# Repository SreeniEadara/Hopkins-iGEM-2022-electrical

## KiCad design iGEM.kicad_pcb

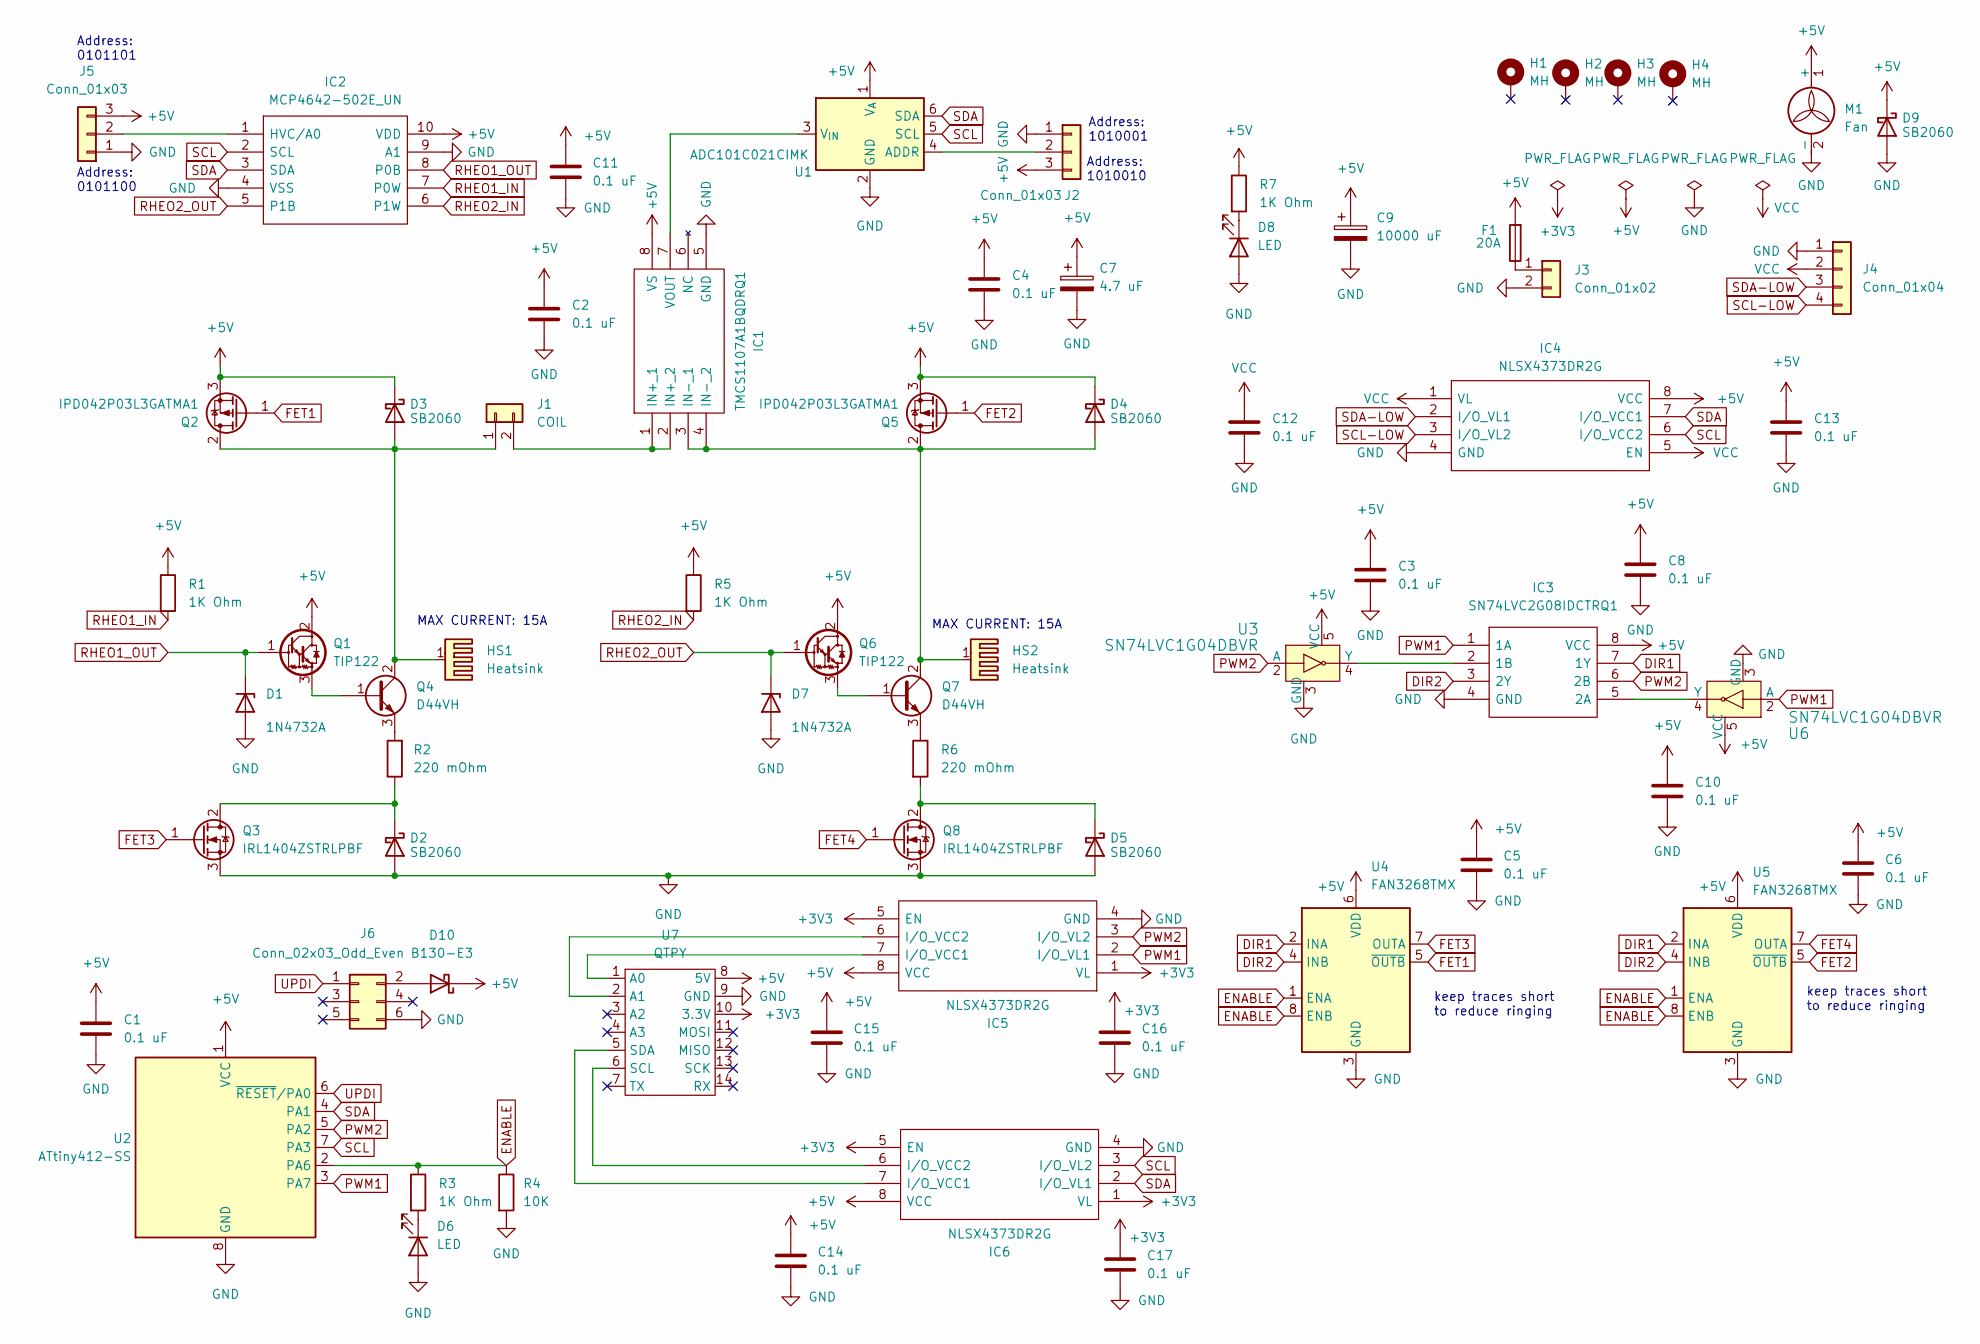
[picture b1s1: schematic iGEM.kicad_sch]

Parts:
C1, C2, C3, C4, C5, C6, C8, C10, C11, C12, C13, C14, C15, C16, C17: 0.1 uF; C_0805_2012Metric_Pad1.18x1.45mm_HandSolder; DigiKey 399-C0805C104K8RAC7800CT-ND
C7: 4.7 uF; CP_EIA-3528-21_Kemet-B_Pad1.50x2.35mm_HandSolder; DigiKey 399-3723-1-ND
C9: 10000 uF; CP_Radial_D22.0mm_P10.00mm_SnapIn; DigiKey 399-ELG109M025AQ4AA-ND
D1, D7: 1N4732A; D_DO-41_SOD81_P10.16mm_Horizontal; DigiKey 1N4732AFSCT-ND
D2, D3, D4, D5, D9: SB2060; D_DO-201AD_P12.70mm_Horizontal; DigiKey 1655-SB2060CT-ND
D6, D8: LED; LED_0805_2012Metric_Pad1.15x1.40mm_HandSolder; DigiKey 475-1410-1-ND
D10: B130-E3; D_SMA; DigiKey B130-E3/5ATGICT-ND
F1: 20A; Fuseholder_Blade_Mini_Keystone_3568; DigiKey 36-3568-15-ND
H1, H2, H3, H4: MH; MountingHole_3.2mm_M3_DIN965_Pad
HS1, HS2: Heatsink; Heatsink_Fischer_SK104-STC-STIC_35x13mm_2xDrill2.5mm; DigiKey HS403-ND
IC1: TMCS1107A1BQDRQ1; SOIC-8_3.9x4.9mm_P1.27mm; Manufacturer_Part_Number TMCS1107A1BQDRQ1; DigiKey 296-TMCS1107A1BQDRQ1CT-ND
IC2: MCP4642-502E_UN; SOP50P490X110-10N; Manufacturer_Part_Number MCP4642-502E/UN; Mouser Part Number 579-MCP4642-502E/UN
IC3: SN74LVC2G08IDCTRQ1; MSOP-8_3x3mm_P0.65mm; Manufacturer_Part_Number SN74LVC2G08IDCTRQ1; Mouser Part Number 595-SN74LVC2G08IDCQ1
IC4, IC5, IC6: NLSX4373DR2G; SOIC-8_3.9x4.9mm_P1.27mm; Manufacturer_Part_Number NLSX4373DR2G; Mouser Part Number 863-NLSX4373DR2G
J1: COIL; TerminalBlock_bornier-2_P5.08mm; DigiKey 102-6218-ND
J2, J5: Conn_01x03; PinHeader_1x03_P2.54mm_Vertical
J3: Conn_01x02; 8PCV02006; DigiKey A98460-ND
J4: Conn_01x04; JST_XH_B4B-XH-A_1x04_P2.50mm_Vertical; DigiKey 455-2249-ND
J6: Conn_02x03_Odd_Even; PinHeader_2x03_P2.54mm_Vertical
M1: Fan; JST_XH_B2B-XH-A_1x02_P2.50mm_Vertical; DigiKey 455-2879-ND
Q1, Q6: TIP122; TO-220-3_Horizontal_TabDown; DigiKey TIP122GOS-ND
Q2, Q5: IPD042P03L3GATMA1; TO-252-2; DigiKey IPD042P03L3GATMA1CT-ND
Q3, Q8: IRL1404ZSTRLPBF; TO-263-2; DigiKey IRL1404ZSTRLPBFCT-ND
Q4, Q7: D44VH; TO-220-3_Vertical; DigiKey D44VH10GOS-ND
R1, R3, R5, R7: 1K Ohm; R_0805_2012Metric_Pad1.20x1.40mm_HandSolder; DigiKey CHP0805-FX-1001ELFCT-ND
R2, R6: 220 mOhm; TerminalBlock_bornier-2_P5.08mm; DigiKey A102180-ND
R4: 10K; R_0805_2012Metric_Pad1.20x1.40mm_HandSolder; DigiKey RMCF0805FT10K0CT-ND
U1: ADC101C021CIMK; SOT-23-6; DigiKey ADC101C021CIMK/NOPBCT-ND
U2: ATtiny412-SS; SOIC-8_3.9x4.9mm_P1.27mm; DigiKey ATTINY412-SSN-ND
U3, U6: SN74LVC1G04DBVR; SOT-753; MPN SN74LVC1G04DBVR; Digi-Key_PN 296-11599-1-ND
U4, U5: FAN3268TMX; SOIC-8_3.9x4.9mm_P1.27mm; DigiKey FAN3268TMXCT-ND
U7: QTPY; QTPY-RP2040

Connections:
+3V3: C16.1, C17.1, IC5.1 (VL), IC5.5 (EN), IC6.1 (VL), IC6.5 (EN), U7.10 (3.3V)
+5V: C1.1, C2.1, C3.1, C4.1, C5.1, C6.1, C7.1, C8.1, C9.1, C10.1, C11.1, C13.1, C14.1, C15.1, D3.1 (K), D4.1 (K), D9.1 (K), D10.1 (K), F1.2, IC1.8 (VS), IC2.10 (VDD), IC3.8 (VCC), IC4.8 (VCC), IC5.8 (VCC), IC6.8 (VCC), J2.3, J5.3, M1.1 (+), Q1.2 (C), Q2.3 (S), Q5.3 (S), Q6.2 (C), R1.1, R5.1, R7.1, U1.1 (V_{A}), U2.1 (VCC), U3.5 (VCC), U4.6 (VDD), U5.6 (VDD), U6.5 (VCC), U7.8 (5V)
DIR1: IC3.7 (1Y), U4.2 (INA), U5.2 (INA)
DIR2: IC3.3 (2Y), U4.4 (INB), U5.4 (INB)
ENABLE: R3.1, R4.1, U2.2 (PA6), U4.1 (ENA), U4.8 (ENB), U5.1 (ENA), U5.8 (ENB)
FET1: Q2.1 (G), U4.5 (~OUTB)
FET2: Q5.1 (G), U5.5 (~OUTB)
FET3: Q3.1 (G), U4.7 (OUTA)
FET4: Q8.1 (G), U5.7 (OUTA)
GND: C1.2, C2.2, C3.2, C4.2, C5.2, C6.2, C7.2, C8.2, C9.2, C10.2, C11.2, C12.2, C13.2, C14.2, C15.2, C16.2, C17.2, D1.2 (A), D2.2 (A), D5.2 (A), D6.2 (A), D7.2 (A), D8.2 (A), D9.2 (A), IC1.5 (GND), IC2.4 (VSS), IC2.9 (A1), IC3.4 (GND), IC4.4 (GND), IC5.4 (GND), IC6.4 (GND), J2.1, J3.2, J4.1, J5.1, J6.6, M1.2 (-), Q3.3 (S), Q8.3 (S), R4.2, U1.2 (GND), U2.8 (GND), U3.3 (GND), U4.3 (GND), U5.3 (GND), U6.3 (GND), U7.9 (GND)
unnamed: D2.1 (K), Q3.2 (D), R2.1
unnamed: D3.2 (A), HS1.1, J1.1, Q2.2 (D), Q4.2 (C)
unnamed: D4.2 (A), HS2.1, IC1.3 (IN-_1), IC1.4 (IN-_2), Q5.2 (D), Q7.2 (C)
unnamed: D5.1 (K), Q8.2 (D), R6.2
unnamed: D6.1 (K), R3.2
unnamed: D8.1 (K), R7.2
unnamed: D10.2 (A), J6.2
unnamed: F1.1, J3.1
unnamed: IC1.1 (IN+_1), IC1.2 (IN+_2), J1.2
unnamed: IC1.7 (VOUT), U1.3 (V_{IN})
unnamed: IC2.1 (HVC/A0), J5.2
unnamed: IC3.2 (1B), U3.4 (Y)
unnamed: IC3.5 (2A), U6.4 (Y)
unnamed: IC5.6 (I/O_VCC2), U7.2 (A1)
unnamed: IC5.7 (I/O_VCC1), U7.1 (A0)
unnamed: IC6.6 (I/O_VCC2), U7.6 (SCL)
unnamed: IC6.7 (I/O_VCC1), U7.5 (SDA)
unnamed: J2.2, U1.4 (ADDR)
unnamed: Q1.3 (E), Q4.1 (B)
unnamed: Q4.3 (E), R2.2
unnamed: Q6.3 (E), Q7.1 (B)
unnamed: Q7.3 (E), R6.1
PWM1: IC3.1 (1A), IC5.2 (I/O_VL1), U2.3 (PA7), U6.2 (A)
PWM2: IC3.6 (2B), IC5.3 (I/O_VL2), U2.5 (PA2), U3.2 (A)
RHEO1_IN: IC2.7 (P0W), R1.2
RHEO1_OUT: D1.1 (K), IC2.8 (P0B), Q1.1 (B)
RHEO2_IN: IC2.6 (P1W), R5.2
RHEO2_OUT: D7.1 (K), IC2.5 (P1B), Q6.1 (B)
SCL: IC2.2 (SCL), IC4.6 (I/O_VCC2), IC6.3 (I/O_VL2), U1.5 (SCL), U2.7 (PA3)
SCL-LOW: IC4.3 (I/O_VL2), J4.4
SDA: IC2.3 (SDA), IC4.7 (I/O_VCC1), IC6.2 (I/O_VL1), U1.6 (SDA), U2.4 (PA1)
SDA-LOW: IC4.2 (I/O_VL1), J4.3
UPDI: J6.1, U2.6 (~RESET/PA0)
VCC: C12.1, IC4.1 (VL), IC4.5 (EN), J4.2

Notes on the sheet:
Address: 0101101
MAX CURRENT: 15A
keep traces short to reduce ringing
Address: 1010001
Address: 1010010
Address: 0101100

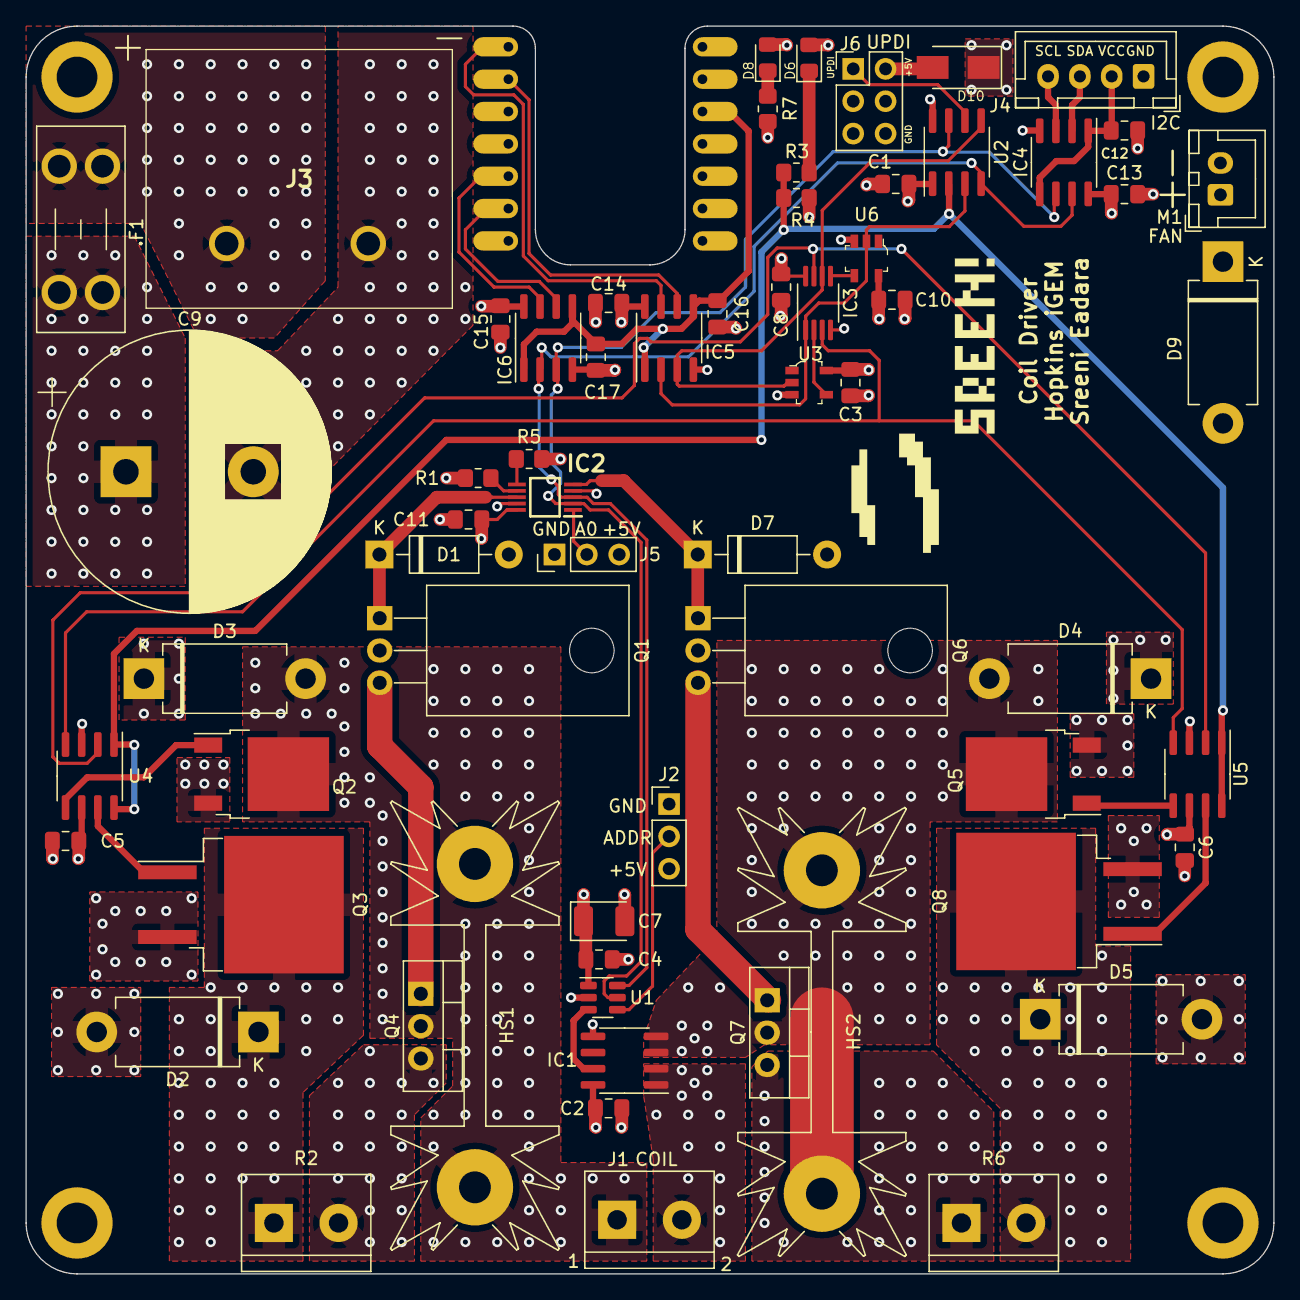
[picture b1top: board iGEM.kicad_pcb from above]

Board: 4 copper layers, 98.0 x 98.0 mm, 69 parts (0 on the bottom side), 44 nets.

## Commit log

2022-06-11 initial commit. Schematic not yet complete
2022-06-11 updated schematic. Added symbols for Adafruit Trinket
2022-07-04 Updated schematic using simulation results and common resistor values. Now using an NPN darlington to drive a D44VH
2022-07-04 changes made to satisfy ERC
2022-07-05 Schematics capture complete. Added footprints and DigiKey part numbers
2022-07-05 layout draft complete
2022-07-05 updated DigiKey part numbers and value of i2c pullups
2022-07-06 cosmetic changes. added designer name
2022-07-06 Added PCA9536D address
2022-07-06 mounting holes no longer connected to signal ground because the chassis will be connected to true earth
2022-07-07 updated mounting holes to M3
2022-07-07 layout cleanup
2022-07-14 increased current capacity and added useful silk
2022-07-18 Changed to a single H-bridge for a single coil. Many parts changes. Addresses now configurable via pin header
2022-07-18 Added indicator LED and updated resistor value
2022-07-18 added bulk capacitance and bug fixes
2022-07-20 Changes to improve thermals and layout
2022-07-21 update layout and heatsink
2022-07-21 Update silk and component position to satisfy ERC
2022-07-22 changing from 6 to 4 layer board. 6 layers is too expensive
2022-07-23 Added LOGOS
2022-07-24 Update LOGO to satisfy DRC
2022-07-24 Adding BOM 'iGEM.csv'
2022-07-24 Adding DigiKey cart csv for ease of purchase. Current total 58.60
2022-07-27 MAJOR LOGIC BUG FIX. Layout also altered
2022-08-01 changed copper pours. Updated BOM and STEP and removed outdated manufacturing files
2022-08-02 miscellaneous changes and cleanup
2022-08-03 Fixed silk
2022-08-05 Added more vias for heat dissipation
2022-08-09 update layout
2022-08-13 adding extra vias for heat dissipation
2022-08-18 Adding level shifter
2022-08-20 Added useful silk and moved fan connector
2022-08-21 Adding inductor to prevent fan voltage spikes
2022-08-23 Adding programming power protection
2022-08-23 updated to include programming power protection and cleanup
2022-08-24 Improved copper balance and cleanup
2022-08-24 adding PCB with curved tracks for style points B) thanks mitxela
2022-08-26 Replace out of stock Stemma QT header
2022-08-29 miscellaneous improvements and cleanup
2022-09-08 Adding QTPY RP2040 as a backup if ATTiny412 does not work
2022-09-10 adding layout with RP2040 QTPY
2022-09-10 updated for clearances
